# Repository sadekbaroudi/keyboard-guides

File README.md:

# Keyboard Guides

A collection of guides I have written to help people in their journey in the ergo mechanical keyboard world!

# About me

## Datasheet

| Category            | Description                                                            |
| ------------------- | ---------------------------------------------------------------------- |
| Name                | Sadek Baroudi                                                          |
| Handle	      | sadekbaroudi, sadekbaroudi#1258                                        |
| Location	      | California, USA                                                        |
| Description	      | Got into ergo mech, started designing, fell in love, never looked back |
| Joined (the hobby)  | 2020                                                                   |
| Niche	              | Unibody splits                                                         |
| Favorite switch(es) | Momoka Frog v3s, Gateron Red Ink V2s,Gateron KS-3 Milky Yellow Pros    |
| Keycap profile(s)   | MT3, DES                                                               |
| Links               | https://fingerpunch.xyz/ https://github.com/sadekbaroudi https://fingerpunch.xyz/discord https://reddit.com/u/sadekbaroudi |

## My keyboards

I have a collection of keyboards, but the ones I use primarily are:
* ffkb v3 ( https://fingerpunch.xyz/product/faux-fox-keyboard-v3/ )
* rock on v3.1 ( https://fingerpunch.xyz/product/rock-on-v3 )

## Credentials

Some of my credentials:
* Creator and maintainer of https://fingerpunch.xyz
* Author of all firmware for fingerpunch boards running QMK and ZMK. See: https://github.com/sadekbaroudi/qmk_firmware/tree/master/fingerpunch and https://github.com/sadekbaroudi/ (search for zmk-*)
* Creator and maintainer of the fingerpunch discord server: https://fingerpunch.xyz/discord
* Active in the keyboard community (reddit, discord, etc)

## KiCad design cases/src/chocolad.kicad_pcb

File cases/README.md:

# Keyboard Case Design

## Overview

In this guide, I'll be providing a detailed walkthrough of how I design 3D models for cases, with the intent of 3D printing them. This starts with a completed keyboard PCB from the Kicad files and ends with a Fusion 360 model that you can export as an STL/3mf for 3D printing. For this guide, I'll be using the Chocolad as an example. As of writing this sentence, I haven't designed the case yet!

https://github.com/jimmerricks/chocolad

## Prerequisites

* You have a basic understanding of Kicad
* You have Inkscape installed (only used to convert SVG to DXF in a way that Fusion 360 can consume)
* You have Fusion 360 installed

## Follow along

I have included the kicad_pcb file used in this example. So, if you'd like to follow along with the instructions below, you can create the same exact case I did! I find that it's a good way to validate what you're reading, and gives you experience for the next case you make.

Navigate to the [src](src/) directory to see the files.

## Walkthrough

### Kicad

Kicad is a perfect place to start, as it provides you with exact dimensions to create a case. This includes, but is not limited to:

* PCB outline
* Switch locations
* Reset switch location
* On/off switch location (for wireless builds)
* Controller location and dimensions
* Rotary encoders
* OLED
* etc

---

### PCB footprints

So, let's first look at the PCB to make sure it has everything we need to consider when doing the initial sketch for the case. You'll want to hide the copper layers so you can clearly see the PCB and footprints to identify what you care about for the case.

---

### Case considerations

There are 5 considerations when looking at this particular PCB:
1) The keyswitch cutouts
2) The edge cuts of the PCB
3) The mounting holes for the M2 standoffs
4) The opening for the controller, TRRS, reset switch
5) The EC11 encoders

(Optional) Also note that there are 4 mounting holes for the tenting puck, which I did not include in the screenshot.

---

### Deselect layers

At this point, you want to deselect layers until you have everything you need while keeping as little showing as possible otherwise. In this case, `User.Eco2`, `Edge.Cuts`, and `F.Courtyard` leave us with almost everything. The only thing missing is the mounting holes.

---

### Update footprints

There was no good layer to expose the mounting holes without exposing way too much from the PCB. It's important not to expose too much, because we'll be exporting this as an SVG. By leaving too much, you have to do a lot more cleanup in SVG later. This is a tedious process, so let's add some drawings to the mounting hole footprints using one of the layers that we've identified in a previous step.

So, here we edit the footprint and add a circle centered around the mounting hole on the `User.Eco2` layer since we're exporting that already. Do this for each of the mounting holes.

(Optional) As noted earlier, you could follow the same process for the tenting puck mounting holes, and include them in the bottom plate. This would allow you to mount a tenting puck to the bottom plate of the case.

---

### Export SVG

Now, we export an SVG and include only the layers we identified earlier.

---

### Save as DXF

You don't have to use Inkscape, but I've found that Inkscape is very reliable in giving us a usable DXF file for Fusion 360. Use the R14 format, and make sure it's set to mm as the unit.

---

### Enable capture design history

If you already use Fusion 360, you may already have this enabled, but if you don't, it's really good to enable this before you get started. Otherwise, it will be hard to make adjustments later!

---

### Import DXF into Fusion 360

Now we go into Fusion 360 and import the DXF we just saved from Inkscape.

---

### Check switch hole size

Check the size of the switch holes. For choc switches, they should be 13.95mm. For MX switches, 14mm works great. If you are doing this for a PCB that supports both choc and MX, 14mm is fine. It feels a bit loose for choc switches, but it'll still work fine.

---

### Adjust switch hole size

If they are not correct, select all the switch holes, and offset them by whatever distance you need to make them 13.95mm or 14mm.

---

### Switch hole size confirmation

Now confirm that the switch holes are correct!

---

### Fix edges

Look around the perimeter of the board and make sure it's a continuous shape. If you see anything that needs some adjustment, fix it in the sketch. In this case, there is an extra curve that we don't want, so let's remove that and make it a straight line.

---

### Mounting hole cleanup

Now we need to adjust the mounting hole size to be correct. Most boards use M2 standoffs, so the hole for the screws here should have a diameter of 2.5mm. Draw a line down the center to identify the center point. Then place a point in the center. Once you do that, you can delete the existing circle and line.

---

### Create new mounting holes

Now that you have a point, draw a center circle around that point, with a diameter of 2.5mm. Repeat this for all of the mounting holes on the board.

---

### Case outline offsets

At this point, we want to select the perimeter of the case, and offset it by about 1mm. If you don't do this, the PCB may not fit in the case, as you want to leave room for error from the PCB manufacturing process.

In the last step, we created the case **inner** wall. Now we need to create the outer wall. You should do the same exact thing you did in the previous step, but increase the offset value. If you want a 2mm thick wall in your case, select 3mm. If you want larger, increase the value as much as you like!

---

### Switch plate extrude

At this point, we want to extrude the plate. You should select everything but the switch holes, mounting holes, and any other area that protrudes above the switch plate. In this case, we want to exclude the region that has the controller, TRRS, and reset switch. This should generally be a thickness of 1.6mm. You can go thicker, but I don't recommend going higher than 2mm.

---

### Wall extrude

Now you want to extrude the walls in the region we offset earlier. The height of this is very important. You don't want to go too short, but you don't want to go much taller than you need. My general rule of thumb is:
* For choc switches, 3mm if soldered, and 4.5mm if hotswap
* For MX switches, 6.5mm if soldered, 8mm if hotswap

You can experiment with values until you get what you're looking for.

---

### Add style and texture

I usually like to add some texture to the outline, but this is a stylistic preference, so feel free to adapt it, or skip this step if you don't mind the sharp edges.

---

### Adjust for other components (measure and draw)

So, admittedly, I forgot to account for the depth of the TRRS cable in the case. That said, this actually serves as a great example to illustrate how to solve it. I measure from a known point on the PCB outline, and look at the Y values (in this case). I check the bottom edge of the TRRS port, and the top edge of the TRRS port. Then I offset by a couple of mm or so to make sure there is enough clearance for the TRRS cable end.

---

### Adjust for other components (extrude)

Now that we have drawn the lines and created a region to extrude, we extrude down to give room to plug in the cable.

---

### Create the bottom plate sketch

The last step is to create the bottom plate, which you will use to screw into the body using the mounting holes. This part is very easy! You go back and edit the original sketch. Then you copy the border of the case and the mounting holes.

---

### Extrude the bottom plate

Once you have the plate sketch, you extrude by whatever thickness you like (2mm is a very good sweet spot, but I sometimes do 1.6 for a slightly lower profile keyboard)

---

### Chamfer mounting holes (optional)

If you are using countersunk screws, you can optionally decide to chamfer the mounting to help accommodate that. It helps to create a flush bottom plate. I generally consider this unnecessary, since you will usually use bump-ons, which protrude farther than M2 screw heads. But if you'd like to experiment with this, see the images below as an example. The example is using a 1.6mm bottom plate, which I generally wouldn't recommend if doing this. I'd suggest using at least a 2mm thickness bottom plate.

---

### Complete case

You are done! Export this as an STL, print it, and do a test fit. If you need to make adjustments, you already know all the steps above. Go back into Fusion 360 and edit using the timeline.

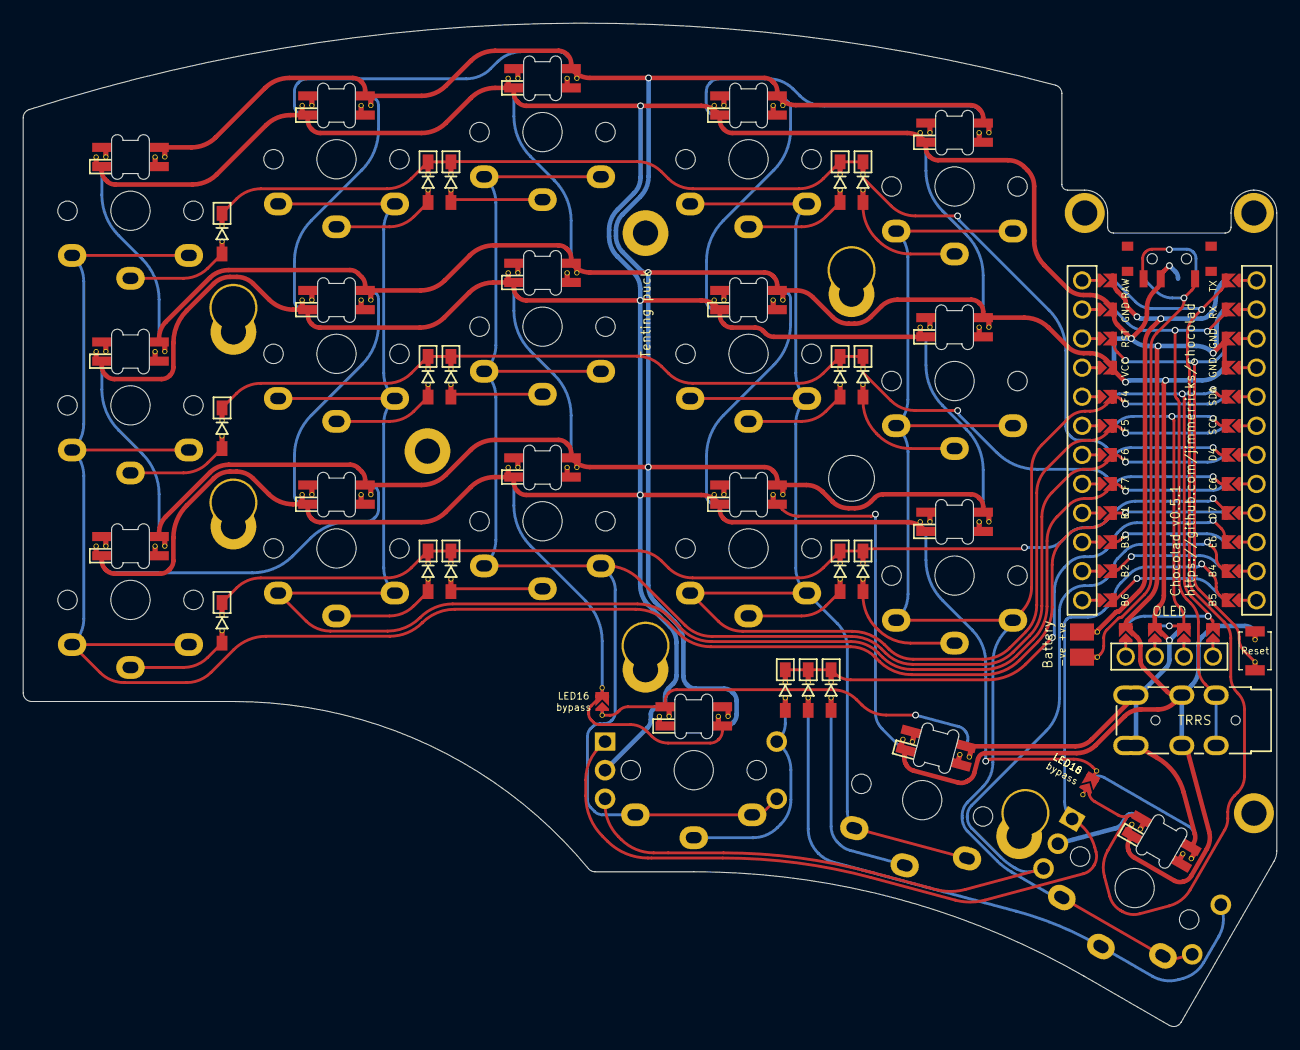
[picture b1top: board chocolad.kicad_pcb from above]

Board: 2 copper layers, 109.5 x 87.7 mm, 73 parts (0 on the bottom side), 55 nets.

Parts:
BT1: Battery_Cell; Battery_pads
D1, D2, D3, D4, D5, D6, D7, D8, D9, D10, D11, D12, D13, D14, D15, D16, D17, D18: D; D3_SMD
EN1, EN2: RotaryEncoder_Switch; RotaryEncoder
H1, H2, H3, H5: M2 Hole; M2_double_hole_4mm
H4: M2_double_hole_4mm
J1: TRRS
JP1, JP2: LED bypass; Jumper
L1: SK6812Mini-e; SK6812_Mini_E
L2, L3, L4, L5, L6, L7, L8, L9, L10, L11, L12, L13, L14, L15, L16, L17, L18: SK6812Mini-e; SK6812_Mini_E_edit
O1: OLED
PSW1: SW_SPDT; Power
PUCK1: SYM_Arrow45_Small; Tenting_puck
RSW1: Reset
Ref**: Val**; M2_hole_3.5mm
Ref**#2, Ref**#3: Val**; M2_hole_3.5mm
SW1, SW2, SW3, SW4, SW5, SW6, SW7, SW8, SW9, SW10, SW11, SW12, SW13, SW14, SW15, SW16, SW17, SW18: SW_PUSH; Choc
U1: ProMicro

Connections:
GND: EN1.C, EN2.C, J1.C, L1.3 (VSS), L2.3 (VSS), L3.3 (VSS), L4.3 (VSS), L5.3 (VSS), L6.3 (VSS), L7.3 (VSS), L8.3 (VSS), L9.3 (VSS), L10.3 (VSS), L11.3 (VSS), L12.3 (VSS), L13.3 (VSS), L14.3 (VSS), L15.3 (VSS), L16.3 (VSS), L17.3 (VSS), L18.3 (VSS), O1.4, PSW1.2 (B), RSW1.2, U1.3 (GND), U1.4 (GND), U1.23 (GND)
LED: JP1.1, L18.4 (DIN), U1.1 (TX)
unnamed: BT1.2 (-), PSW1.1 (A)
unnamed: D1.2 (A), SW1.2
unnamed: D2.2 (A), SW2.2
unnamed: D3.2 (A), SW3.2
unnamed: D4.2 (A), SW4.2
unnamed: D5.2 (A), SW5.2
unnamed: D6.2 (A), SW6.2
unnamed: D7.2 (A), SW7.2
unnamed: D8.2 (A), SW8.2
unnamed: D9.2 (A), SW9.2
unnamed: D10.2 (A), SW10.2
unnamed: D11.2 (A), SW11.2
unnamed: D12.2 (A), SW12.2
unnamed: D13.2 (A), SW13.2
unnamed: D14.2 (A), SW14.2
unnamed: D15.2 (A), SW15.2
unnamed: D17.2 (A), SW17.2
unnamed: L1.4 (DIN), L6.2 (DOUT)
unnamed: L2.2 (DOUT), L7.4 (DIN)
unnamed: L2.4 (DIN), L3.2 (DOUT)
unnamed: L3.4 (DIN), L8.2 (DOUT)
unnamed: L4.2 (DOUT), L9.4 (DIN)
unnamed: L4.4 (DIN), L5.2 (DOUT)
unnamed: L5.4 (DIN), L10.2 (DOUT)
unnamed: L10.4 (DIN), L15.2 (DOUT)
unnamed: L6.4 (DIN), L11.2 (DOUT)
unnamed: L11.4 (DIN), L12.2 (DOUT)
unnamed: L7.2 (DOUT), L12.4 (DIN)
unnamed: L8.4 (DIN), L13.2 (DOUT)
unnamed: L14.2 (DOUT), L17.4 (DIN)
unnamed: L9.2 (DOUT), L14.4 (DIN)
SCL: O1.2, U1.6 (SCL)
SDA: O1.1, U1.5 (SDA)
VCC: J1.A, J1.D, L1.1 (VDD), L2.1 (VDD), L3.1 (VDD), L4.1 (VDD), L5.1 (VDD), L6.1 (VDD), L7.1 (VDD), L8.1 (VDD), L9.1 (VDD), L10.1 (VDD), L11.1 (VDD), L12.1 (VDD), L13.1 (VDD), L14.1 (VDD), L15.1 (VDD), L16.1 (VDD), L17.1 (VDD), L18.1 (VDD), O1.3, U1.21 (VCC)
col0: SW1.1, SW6.1, SW11.1, U1.16 (B1)
col1: SW2.1, SW7.1, SW12.1, U1.17 (F7)
col2: EN1.S1, SW3.1, SW8.1, SW13.1, SW16.1, U1.18 (F6)
col3: SW4.1, SW9.1, SW14.1, SW17.1, U1.19 (F5)
col4: EN2.S1, SW5.1, SW10.1, SW15.1, SW18.1, U1.20 (F4)
data: J1.B, U1.2 (RX)
eda: EN1.A, EN2.A, U1.12 (B5)
edb: EN1.B, EN2.B, U1.11 (B4)
er0: D16.2 (A), EN1.S2, SW16.2
er1: D18.2 (A), EN2.S2, SW18.2
l13i: JP2.2, L13.4 (DIN), L16.2 (DOUT)
l15i: JP1.2, L15.4 (DIN), L18.2 (DOUT)
l17o: JP2.1, L16.4 (DIN), L17.2 (DOUT)
raw: BT1.1 (+), U1.24 (RAW)
reset: RSW1.1, U1.22 (RST)
row0: D1.1 (K), D2.1 (K), D3.1 (K), D4.1 (K), D5.1 (K), U1.7 (D4)
row1: D6.1 (K), D7.1 (K), D8.1 (K), D9.1 (K), D10.1 (K), U1.8 (C6)
row2: D11.1 (K), D12.1 (K), D13.1 (K), D14.1 (K), D15.1 (K), U1.9 (D7)
row3: D16.1 (K), D17.1 (K), D18.1 (K), U1.10 (E6)

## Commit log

2022-11-26 keyboard case guide is complete
2022-11-26 added general readme
2022-11-27 typo in image link to capture design history screenshot
2022-11-28 added notes for tenting puck mounting holes in bottom of case
2023-01-19 added qmk rgb matrix guide
2023-08-07 Updated guide, organized folder
2023-08-08 renamed case sensitivity to match qmk feature name
2023-08-08 added change log with attribution
2023-08-08 Fixed typos, clarified schematic image.
2023-08-08 Fixed typos, clarified wording and 05 schematic image
2023-09-12 docs: improve formatting
